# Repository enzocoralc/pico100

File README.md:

# pico100
small one-handed keyboard

  Compatible with promicro-like boards. This version is mx and choc compatible, both soldered and hotswap.

 This is the current layout for this keyboard:

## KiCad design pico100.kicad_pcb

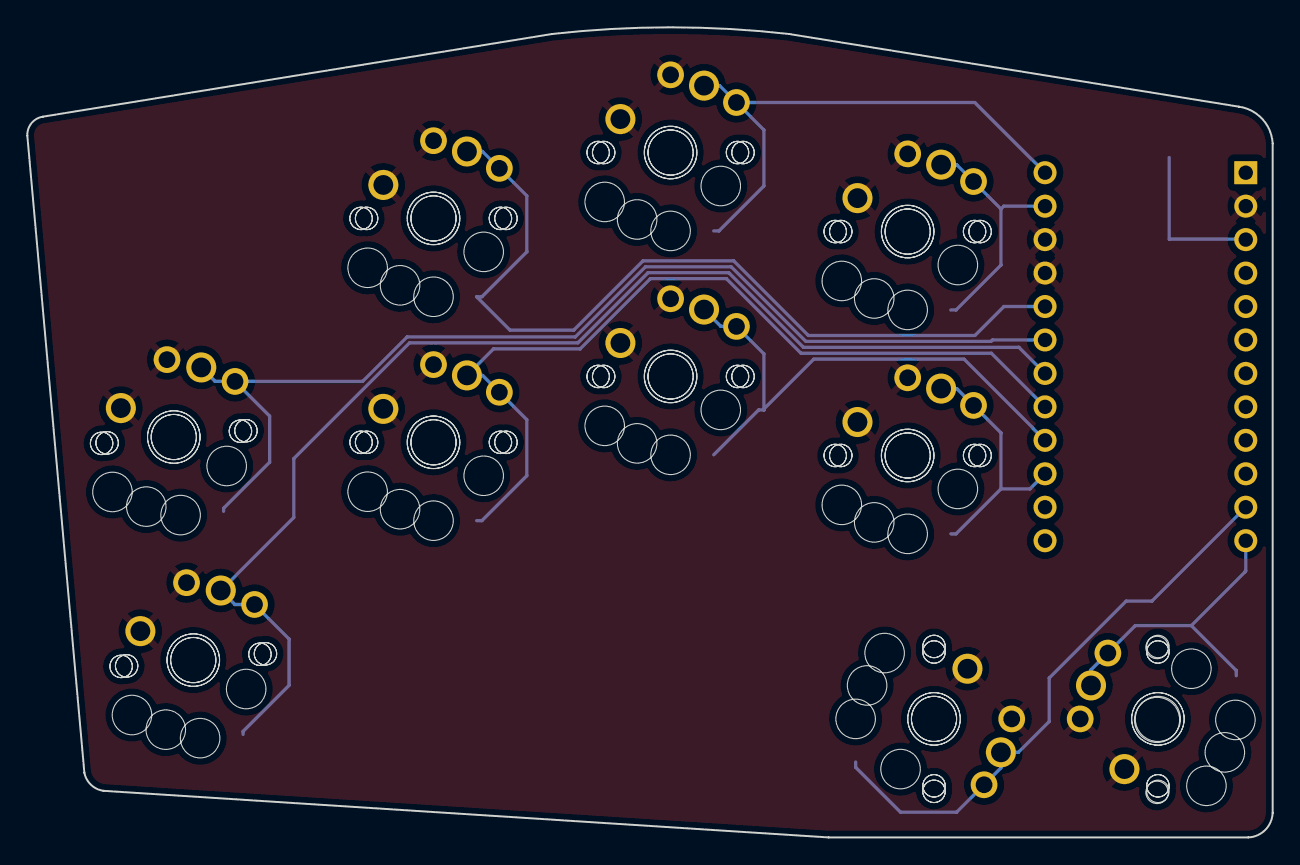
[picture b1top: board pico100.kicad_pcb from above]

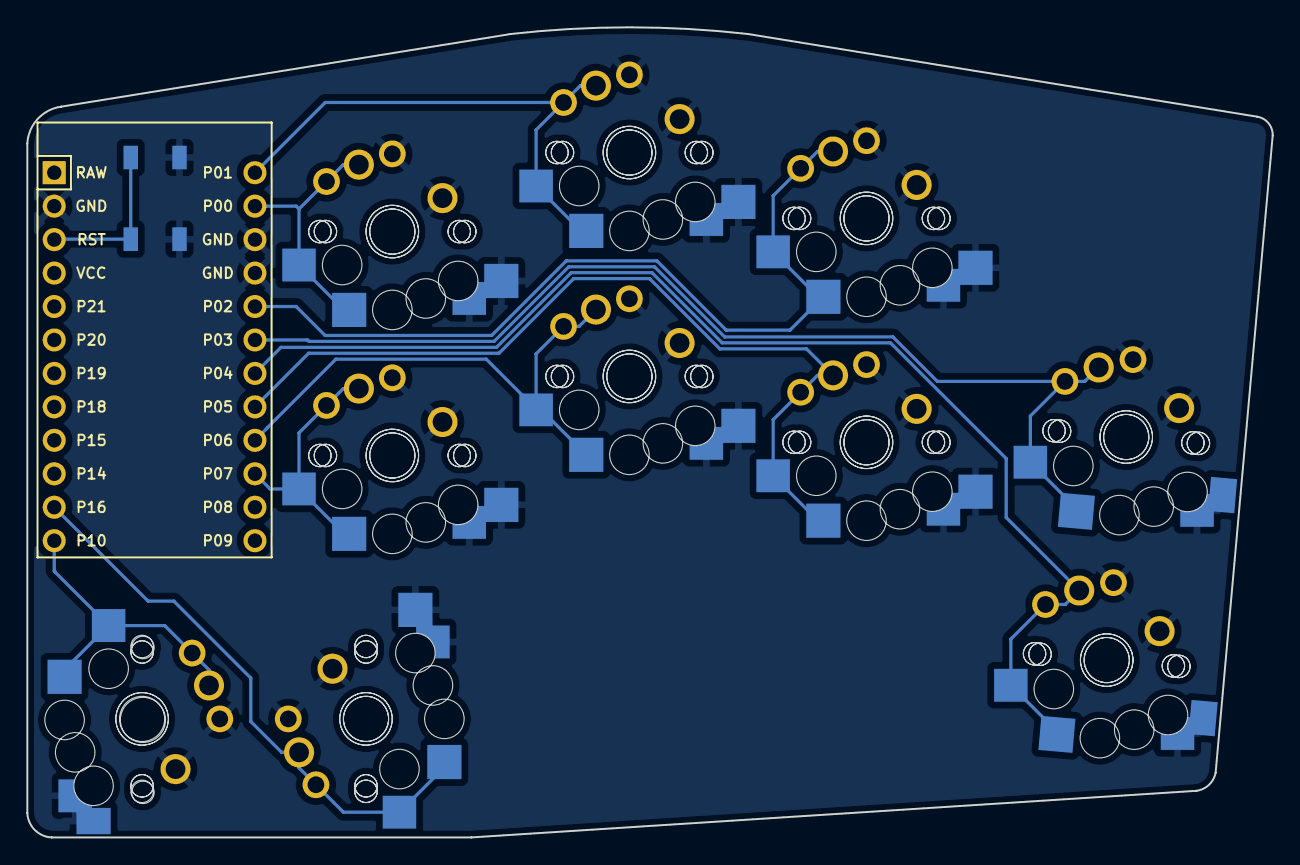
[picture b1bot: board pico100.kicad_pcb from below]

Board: 2 copper layers, 94.6 x 61.5 mm, 42 parts (2 on the bottom side), 12 nets.

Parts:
B1: SW_TACT_ALPS_SKQGABE010
MCU1: ProMicro
S1, S3, S5, S7, S9, S11, S13, S15, S17, S19, S21, S23, S25, S27, S29, S31, S33, S35, S37, S39: PG1350
S2, S4, S6, S8, S10, S12, S14, S16, S18, S20, S22, S24, S26, S28, S30, S32, S34, S36, S38, S40: MX

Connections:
GND: B1.2, MCU1.2, MCU1.15, MCU1.16, S1.2, S2.2, S3.2, S4.2, S5.2, S6.2, S7.2, S8.2, S9.2, S10.2, S11.2, S12.2, S13.2, S14.2, S15.2, S16.2, S17.2, S18.2, S19.2, S20.2, S21.2, S22.2, S23.2, S24.2, S25.2, S26.2, S27.2, S28.2, S29.2, S30.2, S31.2, S32.2, S33.2, S34.2, S35.2, S36.2, S37.2, S38.2, S39.2, S40.2
P0: MCU1.14, S29.1, S30.1, S31.1, S32.1
P1: MCU1.13, S21.1, S22.1, S23.1, S24.1
P2: MCU1.17, S13.1, S14.1, S15.1, S16.1
P3: MCU1.18, S5.1, S6.1, S7.1, S8.1
P4: MCU1.19, S1.1, S2.1, S3.1, S4.1
P5: MCU1.20, S9.1, S10.1, S11.1, S12.1
P6: MCU1.21, S17.1, S18.1, S19.1, S20.1
P7: MCU1.22, S25.1, S26.1, S27.1, S28.1
P10: MCU1.12, S37.1, S38.1, S39.1, S40.1
P16: MCU1.11, S33.1, S34.1, S35.1, S36.1
RST: B1.1, MCU1.3

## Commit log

2021-12-18 added everything
2021-12-18 fixed the layout picture
2021-12-18 fixed layout
2021-12-18 fixed KLE files
2022-01-24 cleaned some traces in the pcb
